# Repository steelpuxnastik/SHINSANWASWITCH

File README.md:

# SHINSANWASWITCH

DIY-friendly photointerrupter microswitch/lamp holder 2-in-1 for generic 100mm Chinese arcade buttons. Enables an OBSA-LHSXF+OBSA-100UMQ-like setup at low cost with generic parts.

## Updates
- This is branch of beta-version SHINSANWASWITCH update version 1.1 with some optimizations that needs to be verified, so now everything is divided into two branches: *main* with stable version 1.0 and version1.1 in *beta* . If you want corrently stable version - use *main* branch. 
Version 1.1 has some optimizations in body of SHINSANWASWITCH and possibility to make different variants of PCB to make with possibility to make one-layered-board at home (if you have anought skill). More info here:  https://www.projectdiva.net/community/threads/shinsanwaswitch-blog-of-creating-diy-analog-of-obsa-lhsxf-ln.2325/page-2#post-18644

## Parts list

### Electrical
Detais about PCB and it's variants can be found in [readme in shinsanwaswitch_PCB thread](shinsanwaswitch_PCB/README.md)

- PCB: 1x `shinsanwaswitch_PCB` **1mm thickness** (KiCad 5.99+ (5.99.0-12455-g28bd734313), release build required for exporting Gerber files or take Gerber files archive in `Gerber/shinsanwaswitch.zip`)
  - C1: Generic 0.1uF through hole ceramic capacitor.
  - C2: *not necessary, but recommended* 47uF 6.3v electrolitic capacitor on the power line input (read [some nuances of board assembly](https://github.com/steelpuxnastik/SHINSANWASWITCH/tree/version1.1/shinsanwaswitch_PCB#some-nuances-of-board-assembly) for more ditails)
  - STI1: `NSI45020AT1G` (for standard and one-layered-board with LED driver board versions) or R4: 470ohm 5% 1/4W through hole (for one-layered-board with resistor and 12v power-up 20mA LED, in other case use calculation to know what resistor you need to use)
  - J1: `S5B-PH-K-S` or equivalent.
  - LED: `S2B-PH-K-S` or equivalent.
  - PC1: `RPI-352`.
  - Q1: `2SC5395-F` or equivalent (may be rare but can be found on e.g. aliexpress).
  - R1: 330ohm 5% 1/4W through hole.
  - R2: 22kohm 5% 1/4W through hole.
  - R3: 10kohm 5% 1/4W through hole.
- 1x harness
  - 5x Single-ended **JST PH** wires (can be found on e.g. aliexpress or alternatively you can crimp them yourself, I recommend you to found on aliexpress for it 5pin 22 AWG white-blue-red-green-black cable, it amazingly fits connector, feels very reliable and also fits into the understandable color scheme)
  - 1x JST `PHR-5` or equivalent.
- 1x LED assembly (no resistors required)
  - 2x **JST PH** to **.1" (BLS-02/Dupont 2pin) female** wires (can be found on e.g. aliexpress or alternatively you can crimp them yourself. I recommend to use wires flexible as possible, that will be very useful. Wires length - somewhere around ~150-160mm, need be shorter as possible, because long wires will be nowhere to fold. Can be made by soldering single-ended JST PH wire and .1" (BLS-02/Dupont 2pin) female wire together and wrapping each wire with heat shrink tubing).
  - 1x 20mA through hole white LED (plugs into the .1" (BLS-02/Dupont 2pin) female connector).
  - 1x JST `PHR-2` or equivalent.
  - 1x 2 pin .1" (BLS-02/Dupont 2pin) female connector housing.
  
### Pin mapping

I/O port (from up to down):

| \#  | Description |
| --- | ----------- |
|  1  | LED+ |
|  2  | LED- |
|  3  | +5V |
|  4  | OUT |
|  5  | GND |

LED connector (from up to down):

| \#  | Description |
| --- | ----------- |
|  1  | + |
|  2  | - |

### Mechanical

- 3D printable parts (printing in resin recommended for best accuracy but not required)
  - 1x `STL/body.STL`
  - 1x `STL/cap.STL`
  - 3x `STL/lever_*.STL` (because of possible differences of generic 100mm Chinese arcade buttons and possible differences in preferences of players that will use it there available 3 different lengts of levers that you should print separately (and better in different colors) and then determine from your own experience what is best for you)
	- 1x `STL/lever_long.STL`
	- 1x `STL/lever_middle.STL`
	- 1x `STL/lever_short.STL`
- 1x 0.3x6x10mm (wire thickness x outer diameter x length) spring (can be found on e.g. aliexpress).
- 2x M2x8 screws

### Example of 3D-print settings that were used
- Layer height: 0.12mm (can be less, but not more, because quality depends on it)
- Nozzle: 0,4mm (can be less, of course)
- Fill level: 25%
- Number of wall lines: 4
- Number of cover layers: 4
- Number of bottom layers: 4
- Supports: only from the bed
- Filament: PETG
- Color: any, but the lever must be black or the part of lever that crosses the optocoupler must be painted with a marker in black in several layers, otherwise the optocoupler will work incorrectly and the switch will not work correctly.

## Source files
In folder `source` there are available source files that used to create 3D-models in SolidWorks. You can use them to make your modification, if you need it.

Original 100mm arcade button Solidworks source files taken from https://grabcad.com/library/100mm-button-1 and very helped me to make this thing.

# Known issues 
At this moment there is no possibility to connect SHINSANWASWITCH (and its active board) to regular matrices, where used connection between different pins, but not pin to ground that used here. If you know how to get around this problem - please, write about that in our issues thread: https://github.com/steelpuxnastik/SHINSANWASWITCH/issues/1

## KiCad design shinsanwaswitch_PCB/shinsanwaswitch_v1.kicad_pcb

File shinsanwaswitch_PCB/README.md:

# SHINSANWASWITCH PCB possible variants

Now there are corrently available three variants of PCB you can use:
- `standard` - two-layered-board with `NSI45020AT1G` LED-driver on the top, use it if you planning to order PCBs on JLCPCB or somewhere else (example of look [front](https://raw.githubusercontent.com/steelpuxnastik/SHINSANWASWITCH/version1.1/source/assimages/6.webp) and [back](https://raw.githubusercontent.com/steelpuxnastik/SHINSANWASWITCH/version1.1/source/assimages/7.webp))
- `LEDDriver_one-layer` - one-layered-board with `NSI45020AT1G` LED-driver, driver places on the bottom of the board, use it if you want to make PCB by yourself at home. (example of look [front](https://raw.githubusercontent.com/steelpuxnastik/SHINSANWASWITCH/version1.1/source/assimages/8.webp) and [back](https://raw.githubusercontent.com/steelpuxnastik/SHINSANWASWITCH/version1.1/source/assimages/9.webp))
- `Resistor_one-layer` - one-layered-board with resistor instead of LED-driver, if you do not want to use/do not have this LED-driver. You need to calculate resistor you need to use based on what input voltage will be used, consumption and voltage of the LED, but be sure that the total power dissipation across the resistor was not more than 1/4W, because board use 1/4W resistor. If you go beyond the power limits described above, you can try to install more powerfull resistor obliquely, but be sure that it will not interfere the installation of the board into the body or if you have problems with this I can recommend you to revise elements you use (use lower input voltage, use other LED or something like that to fit the limits, but if you use our recomendations - more likely you'll have problems with it). (example of look [front](https://raw.githubusercontent.com/steelpuxnastik/SHINSANWASWITCH/version1.1/source/assimages/10.webp) and [back](https://raw.githubusercontent.com/steelpuxnastik/SHINSANWASWITCH/version1.1/source/assimages/11.webp))

# How to open PCB project files?
PCB source files created using KiCad 5.99+ (5.99.0-11737-gca42f31bb5), release build, so you need to use this version of KiCad or newer to open project files. If you use older version - program will not open it.
If you have suitable version, open the main windows of KiCad and click menu "File > Open Project..." or use  Ctrl + O keyboard buttons. In opened window go to ~/shinsanwaswitch_PCB folder and you will see three project files, that are called same as described above:
- `shinsanwaswitch_v1.1-standard.kicad_pro`
- `shinsanwaswitch_v1.1-LEDDriver_one-layer.kicad_pro`
- `shinsanwaswitch_v1.1-Resistor_one-layer.kicad_pro`

So you need to choose what you need project file and then same to open same-named satellite files with PCB or schematic.

# PCB thickness
SHISANWASWITCH body allows to install **only 1mm thickness PCB**. So be sure when you order PCB or if you will make it by yourself, that textolite thickness was 1mm.

# Parts needed

- PCB: 1x `shinsanwaswitch_PCB` **1mm thickness** (one of three possible variants, see [above](#shinsanwaswitch-pcb-possible-variants))
  - C1: Generic 0.1uF through hole ceramic capacitor.
  - C2: *not necessary, but recommended* 47uF 6.3v electrolitic capacitor on the power line input (read [some nuances of board assembly](#some-nuances-of-board-assembly) for more ditails)
  - J1: `S5B-PH-K-S` or equivalent.
  - LED: `S2B-PH-K-S` or equivalent.
  - PC1: `RPI-352`.
  - Q1: `2SC5395-F` or equivalent (may be rare but can be found on e.g. aliexpress).
  - R1: 330ohm 5% 1/4W through hole.
  - R2: 22kohm 5% 1/4W through hole.
  - R3: 10kohm 5% 1/4W through hole.
  - STI1: `NSI45020AT1G` (for `standard` and `LEDDriver_one-layer` board versions) or R4: 470ohm 5% 1/4W through hole (for `Resistor_one-layer` board and 12v power-up 20mA LED, in other case use calculation to know what resistor you need to use)
- 1x harness
  - 5x Single-ended **JST PH** wires (can be found on e.g. aliexpress or alternatively you can crimp them yourself, I recommend you to found on aliexpress for it 5 pin 22 AWG white-blue-red-green-black cable, it amazingly fits connector, feels very reliable and also fits into the understandable color scheme)
  - 1x JST `PHR-5` or equivalent.
- 1x LED assembly (no resistors required)
  - 2x **JST PH** to **.1" (BLS-02/Dupont 2pin) female** wires (can be found on e.g. aliexpress or alternatively you can crimp them yourself. I recommend to use wires flexible as possible, that will be very useful. Wires length - somewhere around ~150-160mm, need be shorter as possible, because long wires will be nowhere to fold. Can be made by soldering single-ended JST PH wire and .1" (BLS-02/Dupont 2pin) female wire together and wrapping each wire with heat shrink tubing).
  - 1x 20mA through hole white LED (plugs into the .1" (BLS-02/Dupont 2pin) female connector).
  - 1x JST `PHR-2` or equivalent.
  - 1x 2 pin .1" (BLS-02/Dupont 2pin) female connector housing.
  
# Pin mapping

I/O port (from up to down):

| \#  | Description |
| --- | ----------- |
|  1  | LED+ |
|  2  | LED- |
|  3  | +5V |
|  4  | OUT |
|  5  | GND |

LED connector (from up to down):

| \#  | Description |
| --- | ----------- |
|  1  | + |
|  2  | - |

# Some nuances of board assembly

- I recommend to start assembly of the board from soldering STI1 (or R4), because of you'll try to do it later, especially after soldering LED and J1 connectors - it will be quite difficult because of small space available.

- I also recommend to cut leads pins of THT-type components to make it shorter as possible before soldering. In body of SHINSANWASWITCH there are available some space to fit the leads pins from the board (according to the drawing - 1.4mm from the board to the bottom of body, but in reality that space can be +/-0.1mm smaller/bigger because of possible nuances of 3D-printing and final installation of board inside the body), so make sure that output leads pins from the PCB does not protrude above ~1mm from the board to eliminate possible problems with installing the board because of that.

- It's not necessary, but recommended to use 47uF 6.3v electrolitic capacitor on the power line input. There is no separated place on board for it's installing, so SMD-type capacitor can be soldered directly to S5B-PH-K-S +5v and GND pins (look [image](https://raw.githubusercontent.com/steelpuxnastik/SHINSANWASWITCH/version1.1/source/assimages/4.webp)). If you use THT-type electrolitic capacitor - you can put leads pins of capacitor directly to +5v and GND pins holes on the board with JST connector, it's possible because for this holes of +5v and GND were enlarged to fit two leads pins in one hole. Make sure that leads pins of capacitor do not contacts other nearby leads pins, for reliability, leads pins of capasitor better to isolate with heat shrinkage before soldering (look [image](https://raw.githubusercontent.com/steelpuxnastik/SHINSANWASWITCH/version1.1/source/assimages/5.webp)).

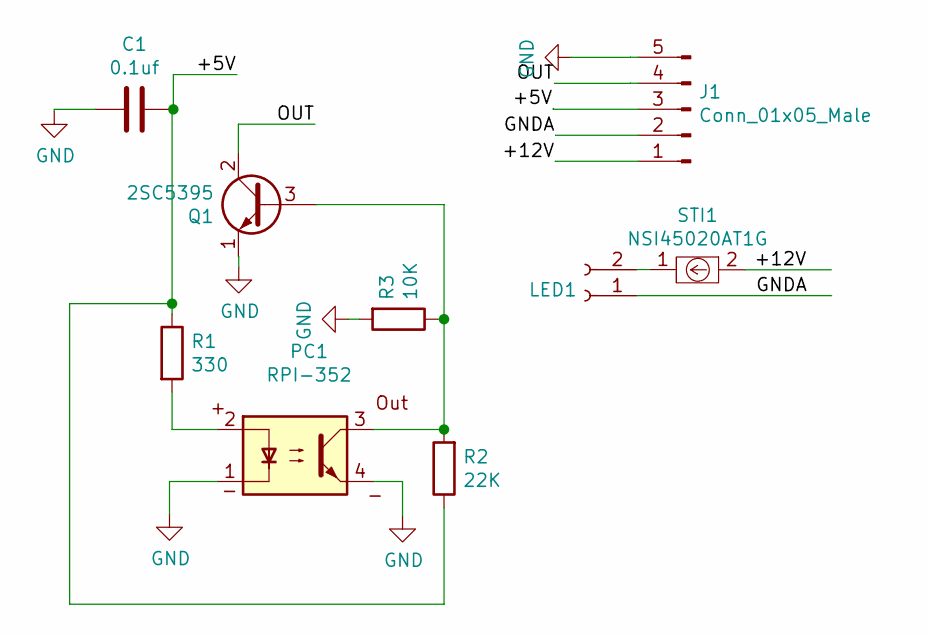
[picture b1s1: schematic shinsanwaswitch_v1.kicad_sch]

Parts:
C1: 0.1uf; C_Disc_D3.8mm_W2.6mm_P2.50mm
J1: Conn_01x05_Male; JST_PH_S5B-PH-K_1x05_P2.00mm_Horizontal
LED1: Conn_01x02_Female; JST_PH_S2B-PH-K_1x02_P2.00mm_Horizontal
PC1: RPI-352
Q1: 2SC5395; TO-92S_Wide
R1: 330; R_Axial_DIN0204_L3.6mm_D1.6mm_P5.08mm_Horizontal
R2: 22K; R_Axial_DIN0204_L3.6mm_D1.6mm_P5.08mm_Horizontal
R3: 10K; R_Axial_DIN0204_L3.6mm_D1.6mm_P5.08mm_Horizontal
STI1: NSI45020AT1G; D_SOD-123

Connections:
/+5V: C1.2, J1.3, R1.1, R2.1
/+12V: J1.1, STI1.2
/GNDA: J1.2, LED1.1
/OUT: J1.4, Q1.2 (C)
GND: C1.1, J1.5, PC1.1, PC1.4, Q1.1 (E), R3.2
unnamed: LED1.2, STI1.1
unnamed: PC1.2, R1.2
unnamed: PC1.3, Q1.3 (B), R2.2, R3.1

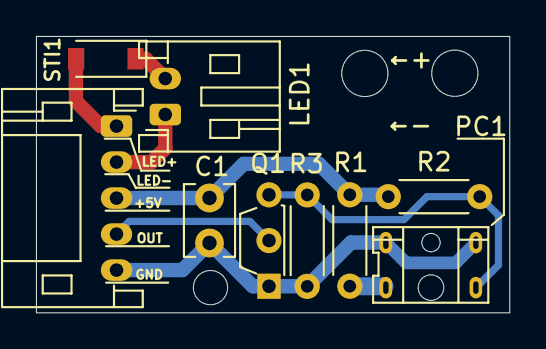
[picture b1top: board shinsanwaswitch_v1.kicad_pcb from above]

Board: 2 copper layers, 26.3 x 15.4 mm, 9 parts (0 on the bottom side), 8 nets.

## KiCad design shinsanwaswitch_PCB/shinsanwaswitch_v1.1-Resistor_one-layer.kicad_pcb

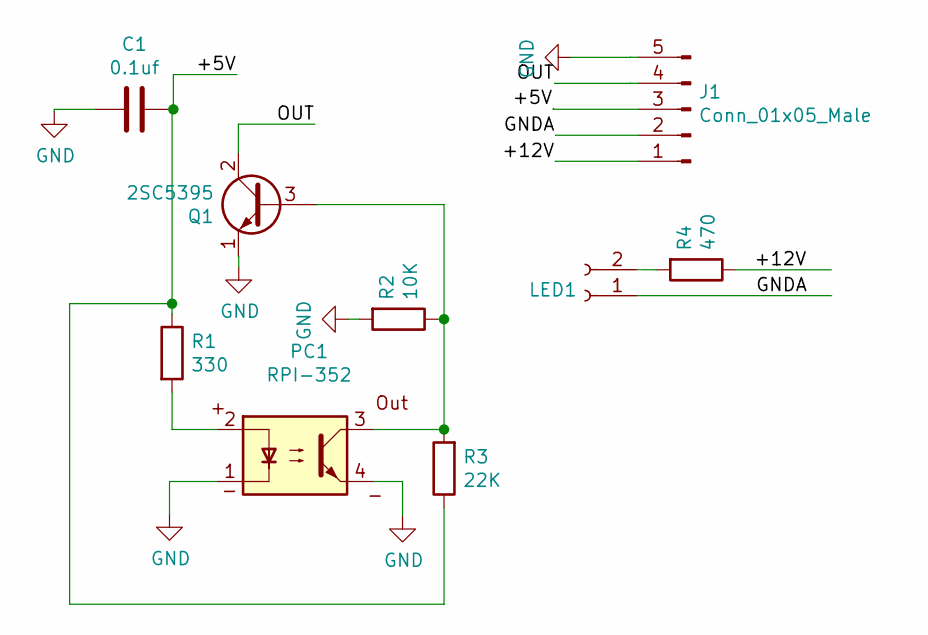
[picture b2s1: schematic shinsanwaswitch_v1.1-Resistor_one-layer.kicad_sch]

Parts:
C1: 0.1uf; C_Disc_D3.8mm_W2.6mm_P2.50mm
J1: Conn_01x05_Male; JST_PH_S5B-PH-K_1x05_P2.00mm_Horizontal
LED1: Conn_01x02_Female; JST_PH_S2B-PH-K_1x02_P2.00mm_Horizontal
PC1: RPI-352; RPI-352_otherholes
Q1: 2SC5395; TO-92S_Wide
R1: 330; R_Axial_DIN0204_L3.6mm_D1.6mm_P5.08mm_Horizontal
R2: 10K; R_Axial_DIN0204_L3.6mm_D1.6mm_P5.08mm_Horizontal
R3: 22K; R_Axial_DIN0204_L3.6mm_D1.6mm_P5.08mm_Horizontal
R4: 470; R_Axial_DIN0204_L3.6mm_D1.6mm_P5.08mm_Horizontal

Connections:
/+5V: C1.2, J1.3, R1.1, R3.1
/+12V: J1.1, R4.1
/GNDA: J1.2, LED1.1
/OUT: J1.4, Q1.2 (C)
GND: C1.1, J1.5, PC1.1, PC1.4, Q1.1 (E), R2.2
unnamed: LED1.2, R4.2
unnamed: PC1.2, R1.2
unnamed: PC1.3, Q1.3 (B), R2.1, R3.2

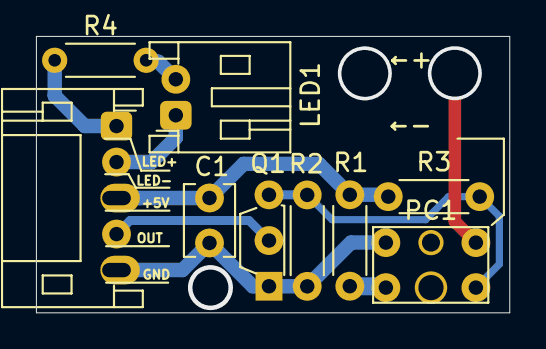
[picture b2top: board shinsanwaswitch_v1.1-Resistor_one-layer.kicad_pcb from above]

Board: 2 copper layers, 26.3 x 15.4 mm, 9 parts (0 on the bottom side), 8 nets.

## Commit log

2021-02-15 Finally uploaded
2021-02-15 Additional
2021-04-19 Add README
2021-06-23 Add parts list to README
    The screw type still needs confirmation.
2021-06-23 Slightly clarify LED requirements
2021-06-23 All the resistors should be through hole too.
2021-07-05 Add screw type.
2021-08-13 Update README.md
    Added 3D-print settings example
2021-08-13 added different levers in diffent lengts
    to find best for you
2021-08-13 Gerber files added
2021-08-18 version 1.1 beta added
2021-08-20 progressive update
2021-08-20 Logo
2021-08-20 board image
2021-08-20 v1.1 update, bigger power line holes
2021-08-20 separation version 1.1 from stable
    Version 1.1 is now on other branch
2021-08-20 version 1.1 only here now
2021-08-22 Readme to PCB
2021-08-22 update gerber
2021-08-22 Assembly info test
2021-08-22 update assembly info
2021-09-03 Update for DIY-make boards
2021-09-22 Massive update of DIY-boards to make it easier to print and drill
2022-03-15 Minor changes for JLCPCB 3D printing
    Only in solidworks for now, later will be confirmed.
2022-03-15 Added lost part
2022-03-16 #StandWithUkraine
2022-04-17 Update to Kicad 6.99 + RPI-352 footprint
